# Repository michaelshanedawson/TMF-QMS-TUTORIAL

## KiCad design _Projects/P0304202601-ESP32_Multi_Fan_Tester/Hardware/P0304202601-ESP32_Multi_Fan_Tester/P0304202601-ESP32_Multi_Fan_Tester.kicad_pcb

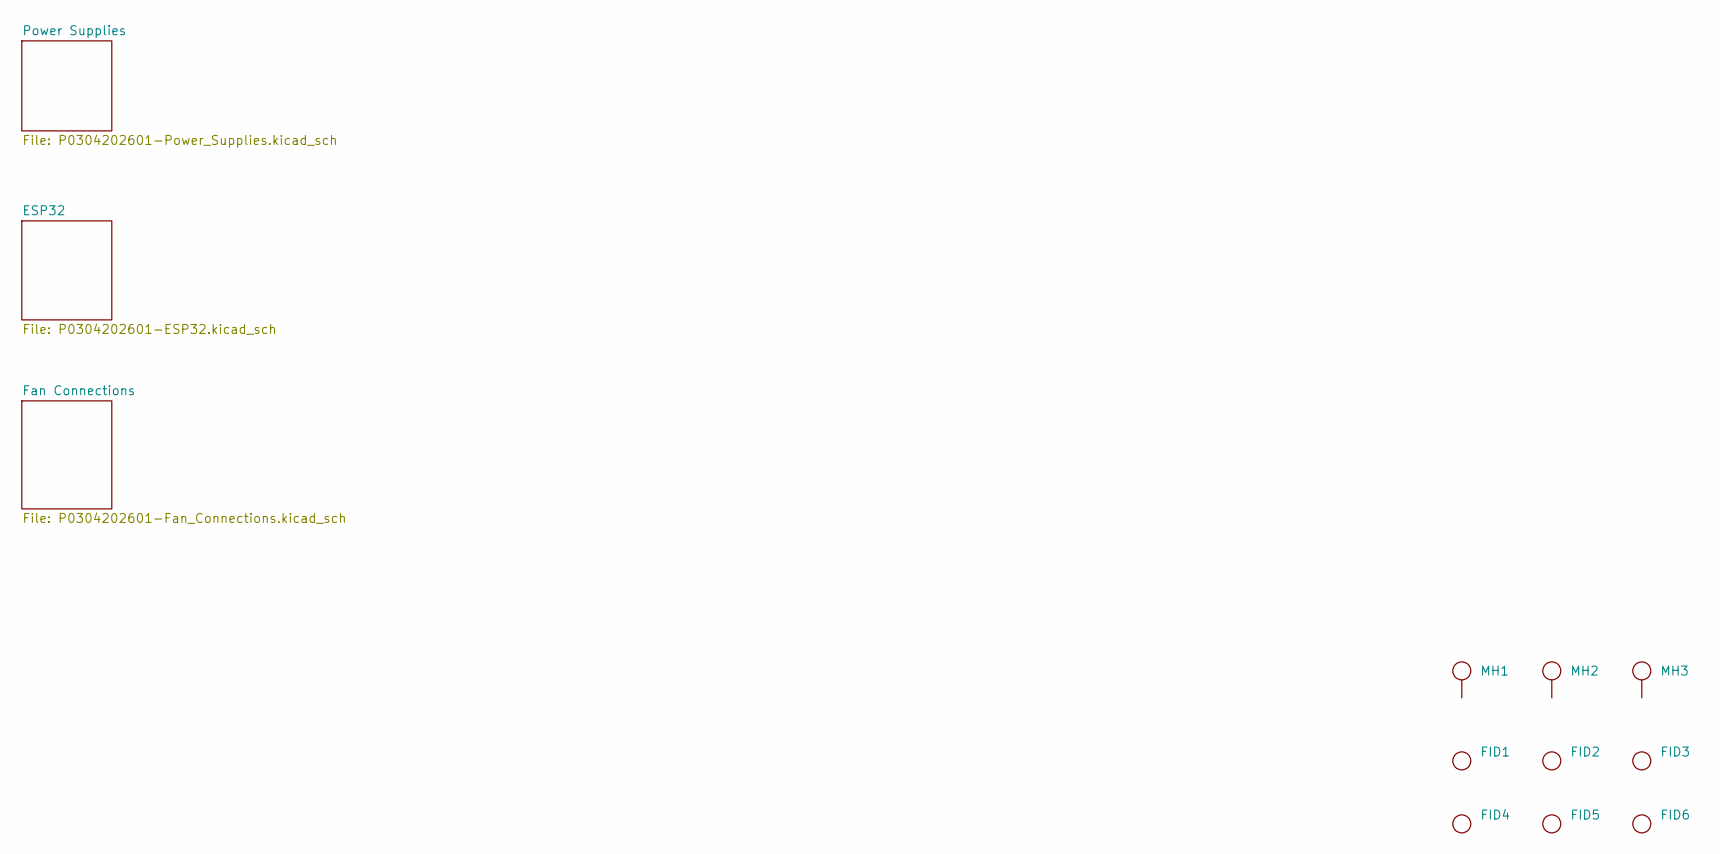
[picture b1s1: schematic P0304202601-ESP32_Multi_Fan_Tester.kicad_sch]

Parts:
FID1, FID2, FID3, FID4, FID5, FID6: FID1.0x1.5mm Round
MH1, MH2, MH3: M3MountingHole

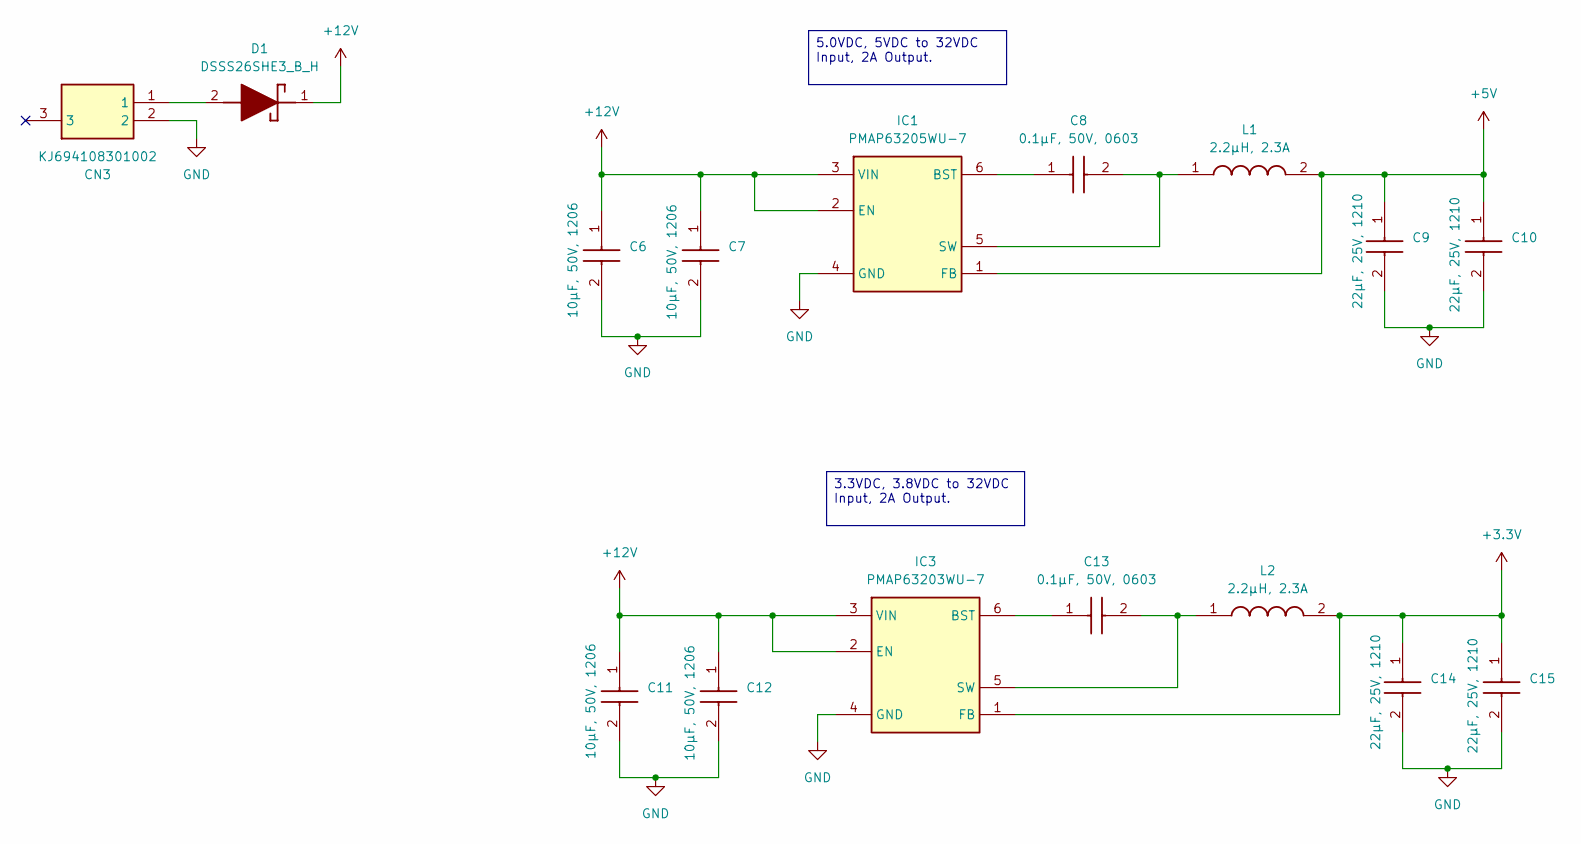
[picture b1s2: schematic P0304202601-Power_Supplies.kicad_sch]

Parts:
C6, C7, C11, C12: CC1206106050AAAX7R; CAP-1206
C8, C13: CC0603104050AAAX7R; CAP-0603
C9, C10, C14, C15: CC1210226025AAAX7R; CAP-1210
CN3: KJ694108301002
D1: DSSS26SHE3_B_H; SMA
IC1: PMAP63205WU-7; TSOT-26-6
IC3: PMAP63203WU-7; TSOT-26-6
L1, L2: LSRP2512-2R2M; IND-1005

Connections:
+3.3V: C14.1, C15.1, IC3.1 (FB), L2.2; also elsewhere on the board
+5V: C9.1, C10.1, IC1.1 (FB), L1.2; also elsewhere on the board
+12V: C6.1, C7.1, C11.1, C12.1, D1.1 (K), IC1.2 (EN), IC1.3 (VIN), IC3.2 (EN), IC3.3 (VIN); also elsewhere on the board
GND: C6.2, C7.2, C9.2, C10.2, C11.2, C12.2, C14.2, C15.2, CN3.2, IC1.4 (GND), IC3.4 (GND); also elsewhere on the board
unnamed: CN3.1, D1.2 (A)
unnamed: C8.1, IC1.6 (BST)
unnamed: C8.2, IC1.5 (SW), L1.1
unnamed: C13.1, IC3.6 (BST)
unnamed: C13.2, IC3.5 (SW), L2.1

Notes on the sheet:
5.0VDC, 5VDC to 32VDC Input, 2A Output.
3.3VDC, 3.8VDC to 32VDC Input, 2A Output.

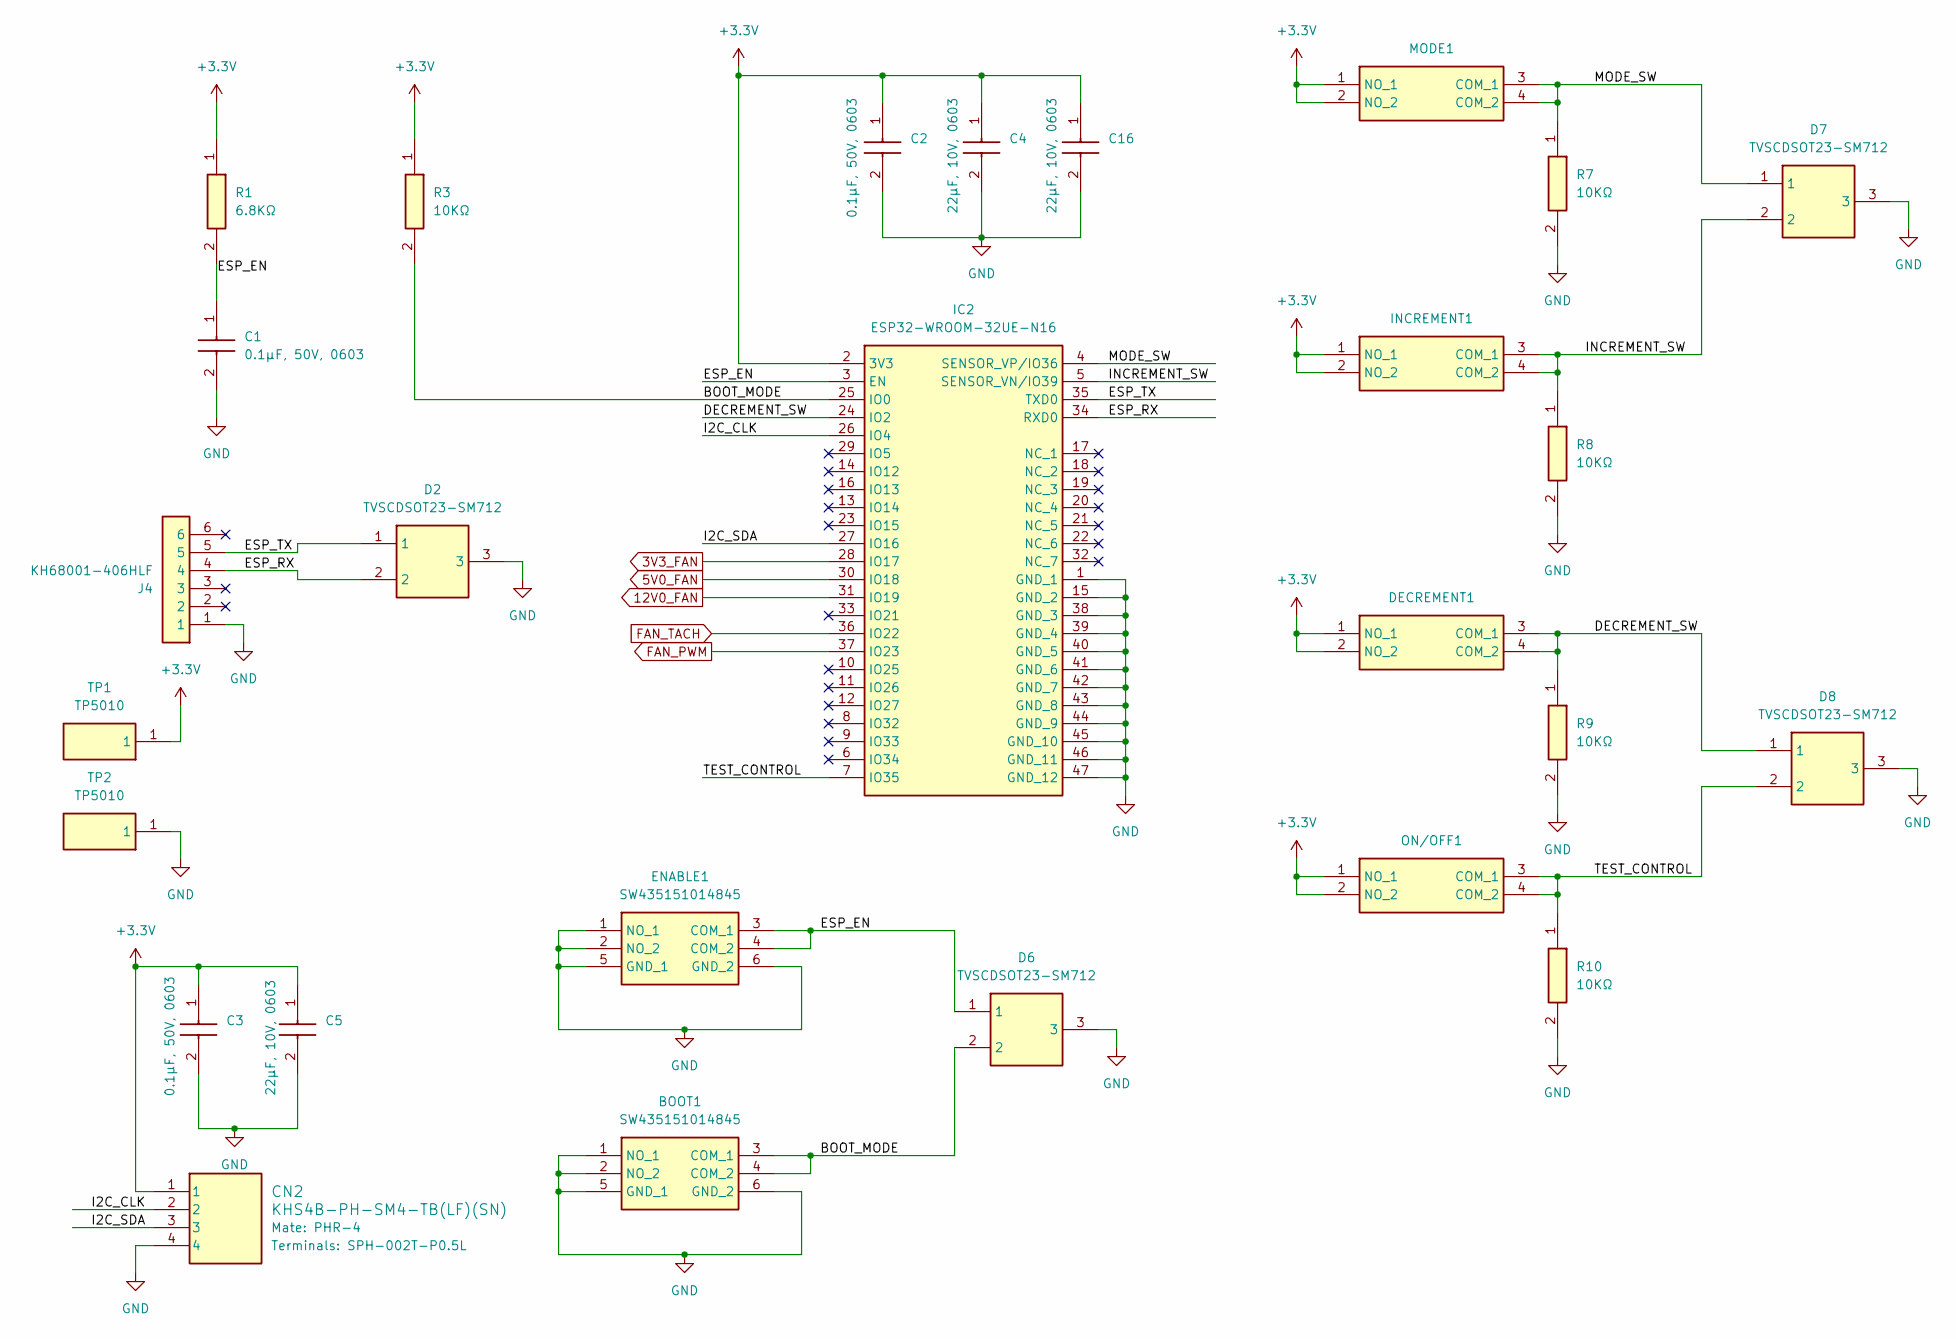
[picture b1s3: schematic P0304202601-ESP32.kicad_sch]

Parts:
BOOT1: SW435151014845; 435151014845
C1, C2, C3: CC0603104050AAAX7R; CAP-0603
C4, C5, C16: CC0603226010AABX5R; CAP-0603
CN2: KHS4B-PH-SM4-TB(LF)(SN); S4B-PH-SM4-TB
D2, D6, D7, D8: TVSCDSOT23-SM712; SOT-23-3
DECREMENT1: TS14121260BK260SCRD
ENABLE1: SW435151014845; 435151014845
IC2: ESP32-WROOM-32UE-N16; ESP32WROOM32UE
INCREMENT1: TS14121260BK260SCRD
J4: KH68001-406HLF; 6x1HDR2.54mm
MODE1: TS14121260BK260SCRD
ON/OFF1: TS14121260BK260SCRD
R1: RC0603682075AAA; RES-0603
R3, R7, R8, R9, R10: RC060310K2075AAA; RES-0603
TP1, TP2: TP5010; 5010

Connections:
3V3_FAN: IC2.28 (IO17); also elsewhere on the board
5V0_FAN: IC2.30 (IO18); also elsewhere on the board
12V0_FAN: IC2.31 (IO19); also elsewhere on the board
+3.3V: C2.1, C3.1, C4.1, C5.1, C16.1, CN2.1, DECREMENT1.1 (NO_1), DECREMENT1.2 (NO_2), IC2.2 (3V3), INCREMENT1.1 (NO_1), INCREMENT1.2 (NO_2), MODE1.1 (NO_1), MODE1.2 (NO_2), ON/OFF1.1 (NO_1), ON/OFF1.2 (NO_2), R1.1, R3.1, TP1.1 (1_1); also elsewhere on the board
/ESP32/BOOT_MODE: BOOT1.3 (COM_1), BOOT1.4 (COM_2), D6.2, IC2.25 (IO0), R3.2
/ESP32/DECREMENT_SW: D8.1, DECREMENT1.3 (COM_1), DECREMENT1.4 (COM_2), IC2.24 (IO2), R9.1
/ESP32/ESP_EN: C1.1, D6.1, ENABLE1.3 (COM_1), ENABLE1.4 (COM_2), IC2.3 (EN), R1.2
/ESP32/ESP_RX: D2.2, IC2.34 (RXD0), J4.4
/ESP32/ESP_TX: D2.1, IC2.35 (TXD0), J4.5
/ESP32/I2C_CLK: CN2.2, IC2.26 (IO4)
/ESP32/I2C_SDA: CN2.3, IC2.27 (IO16)
/ESP32/INCREMENT_SW: D7.2, IC2.5 (SENSOR_VN/IO39), INCREMENT1.3 (COM_1), INCREMENT1.4 (COM_2), R8.1
/ESP32/MODE_SW: D7.1, IC2.4 (SENSOR_VP/IO36), MODE1.3 (COM_1), MODE1.4 (COM_2), R7.1
/ESP32/TEST_CONTROL: D8.2, IC2.7 (IO35), ON/OFF1.3 (COM_1), ON/OFF1.4 (COM_2), R10.1
FAN_PWM: IC2.37 (IO23); also elsewhere on the board
FAN_TACH: IC2.36 (IO22); also elsewhere on the board
GND: BOOT1.1 (NO_1), BOOT1.2 (NO_2), BOOT1.5 (GND_1), BOOT1.6 (GND_2), C1.2, C2.2, C3.2, C4.2, C5.2, C16.2, CN2.4, D2.3, D6.3, D7.3, D8.3, ENABLE1.1 (NO_1), ENABLE1.2 (NO_2), ENABLE1.5 (GND_1), ENABLE1.6 (GND_2), IC2.1 (GND_1), IC2.15 (GND_2), IC2.38 (GND_3), IC2.39 (GND_4), IC2.40 (GND_5), IC2.41 (GND_6), IC2.42 (GND_7), IC2.43 (GND_8), IC2.44 (GND_9), IC2.45 (GND_10), IC2.46 (GND_11), IC2.47 (GND_12), J4.1, R7.2, R8.2, R9.2, R10.2, TP2.1 (1_1); also elsewhere on the board

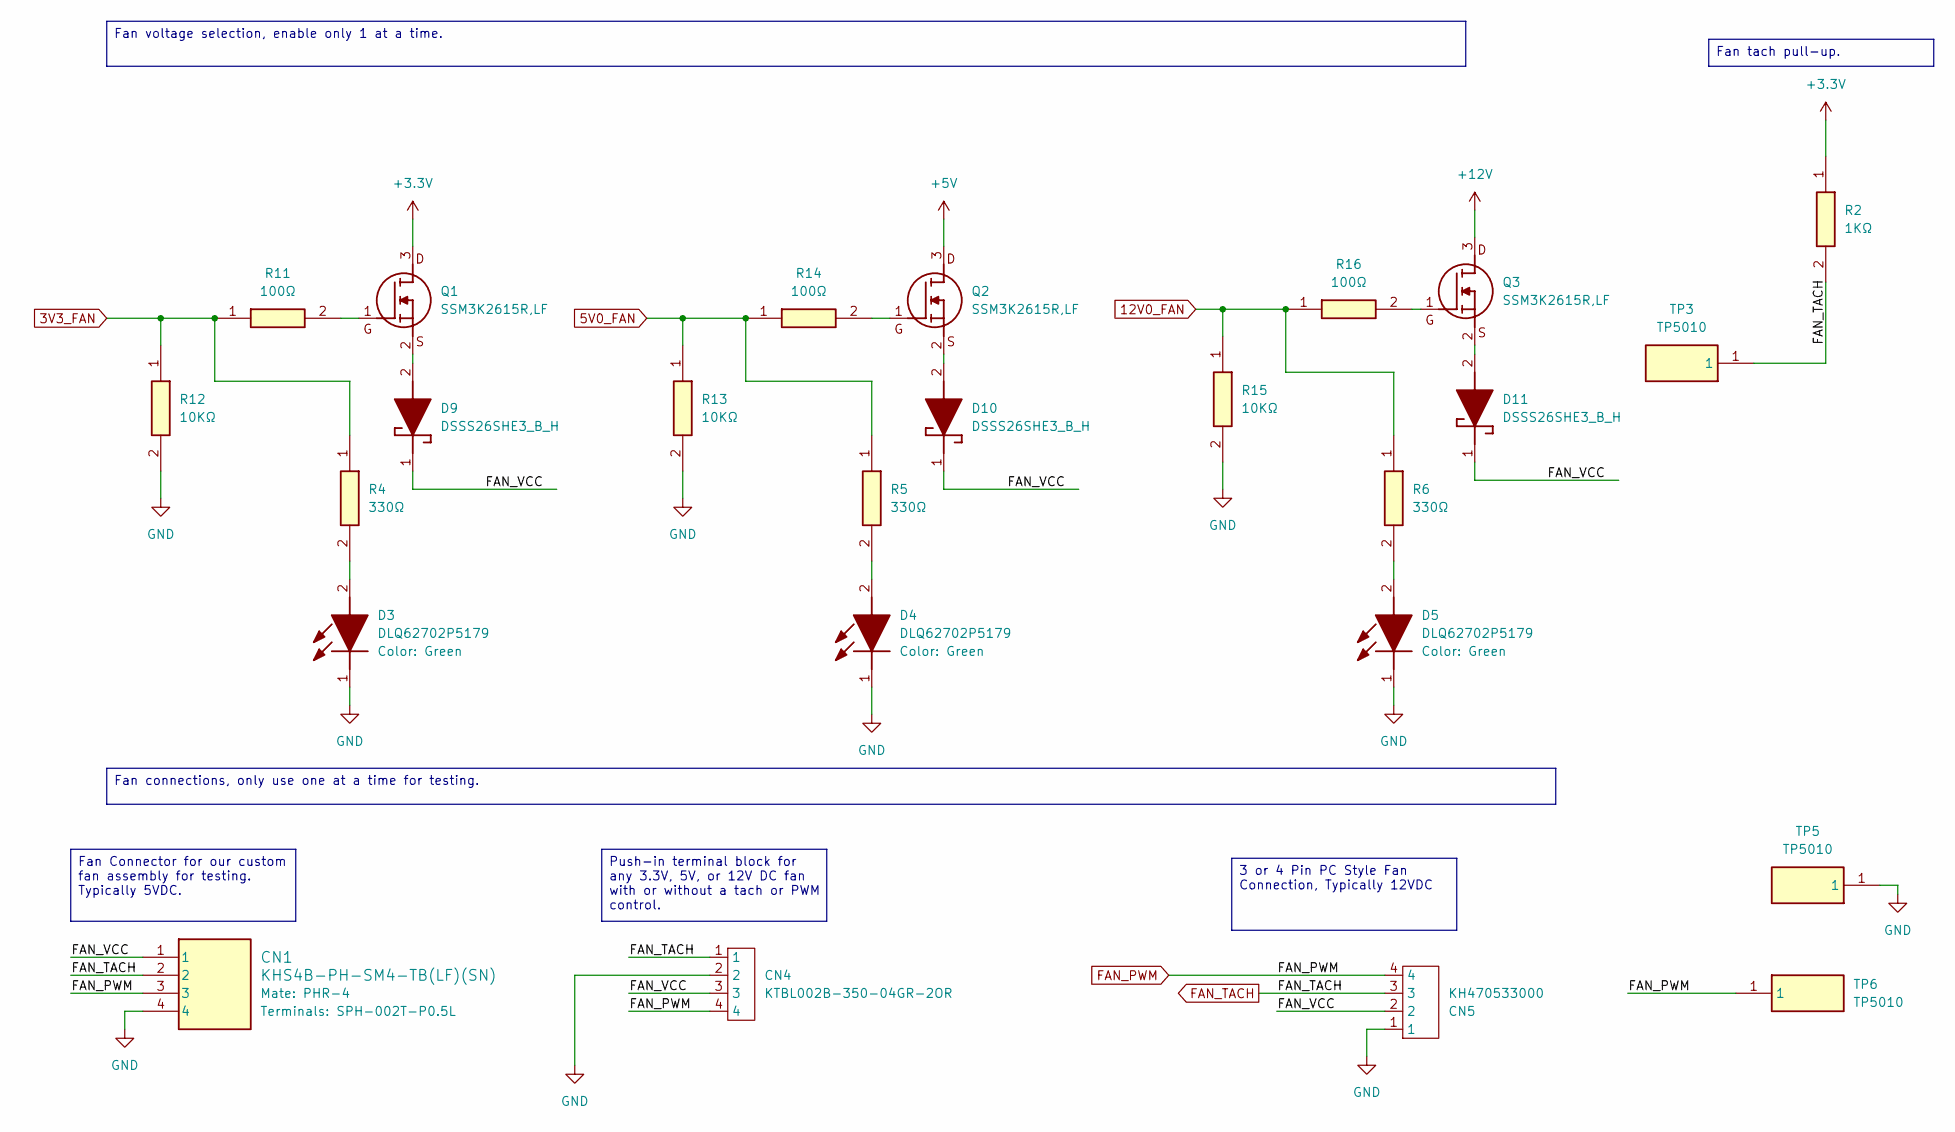
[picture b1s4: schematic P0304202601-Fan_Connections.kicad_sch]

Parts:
CN1: KHS4B-PH-SM4-TB(LF)(SN); S4B-PH-SM4-TB
CN4: KTBL002B-350-04GR-2OR; KTBTBL002B35004GR2OR
CN5: KH470533000
D3, D4, D5: DLQ62702P5179; LED-0805
D9, D10, D11: DSSS26SHE3_B_H; SMA
Q1, Q2, Q3: SSM3K2615R,LF; SOT-23F-3
R2: RC06031K0075AAA; RES-0603
R4, R5, R6: RC0603330075AAA; RES-0603
R11, R14, R16: 100Ω; RES-0603
R12, R13, R15: RC060310K2075AAA; RES-0603
TP3, TP5, TP6: TP5010; 5010

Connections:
3V3_FAN: R4.1, R11.1, R12.1; also elsewhere on the board
5V0_FAN: R5.1, R13.1, R14.1; also elsewhere on the board
12V0_FAN: R6.1, R15.1, R16.1; also elsewhere on the board
+3.3V: Q1.3 (D), R2.1; also elsewhere on the board
+5V: Q2.3 (D); also elsewhere on the board
+12V: Q3.3 (D); also elsewhere on the board
/Fan Connections/FAN_VCC: CN1.1, CN4.3, CN5.2, D9.1 (K), D10.1 (K), D11.1 (K)
FAN_PWM: CN1.3, CN4.4, CN5.4, TP6.1 (1_1); also elsewhere on the board
FAN_TACH: CN1.2, CN4.1, CN5.3, R2.2, TP3.1 (1_1); also elsewhere on the board
GND: CN1.4, CN4.2, CN5.1, D3.1 (K), D4.1 (K), D5.1 (K), R12.2, R13.2, R15.2, TP5.1 (1_1); also elsewhere on the board
unnamed: D3.2 (A), R4.2
unnamed: D4.2 (A), R5.2
unnamed: D5.2 (A), R6.2
unnamed: D9.2 (A), Q1.2 (S)
unnamed: D10.2 (A), Q2.2 (S)
unnamed: D11.2 (A), Q3.2 (S)
unnamed: Q1.1 (G), R11.2
unnamed: Q2.1 (G), R14.2
unnamed: Q3.1 (G), R16.2

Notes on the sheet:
Fan Connector for our custom fan assembly for testing. Typically 5VDC.
3 or 4 Pin PC Style Fan Connection, Typically 12VDC
Fan tach pull-up.
Fan connections, only use one at a time for testing.
Push-in terminal block for any 3.3V, 5V, or 12V DC fan with or without a tach or PWM control.
Fan voltage selection, enable only 1 at a time.

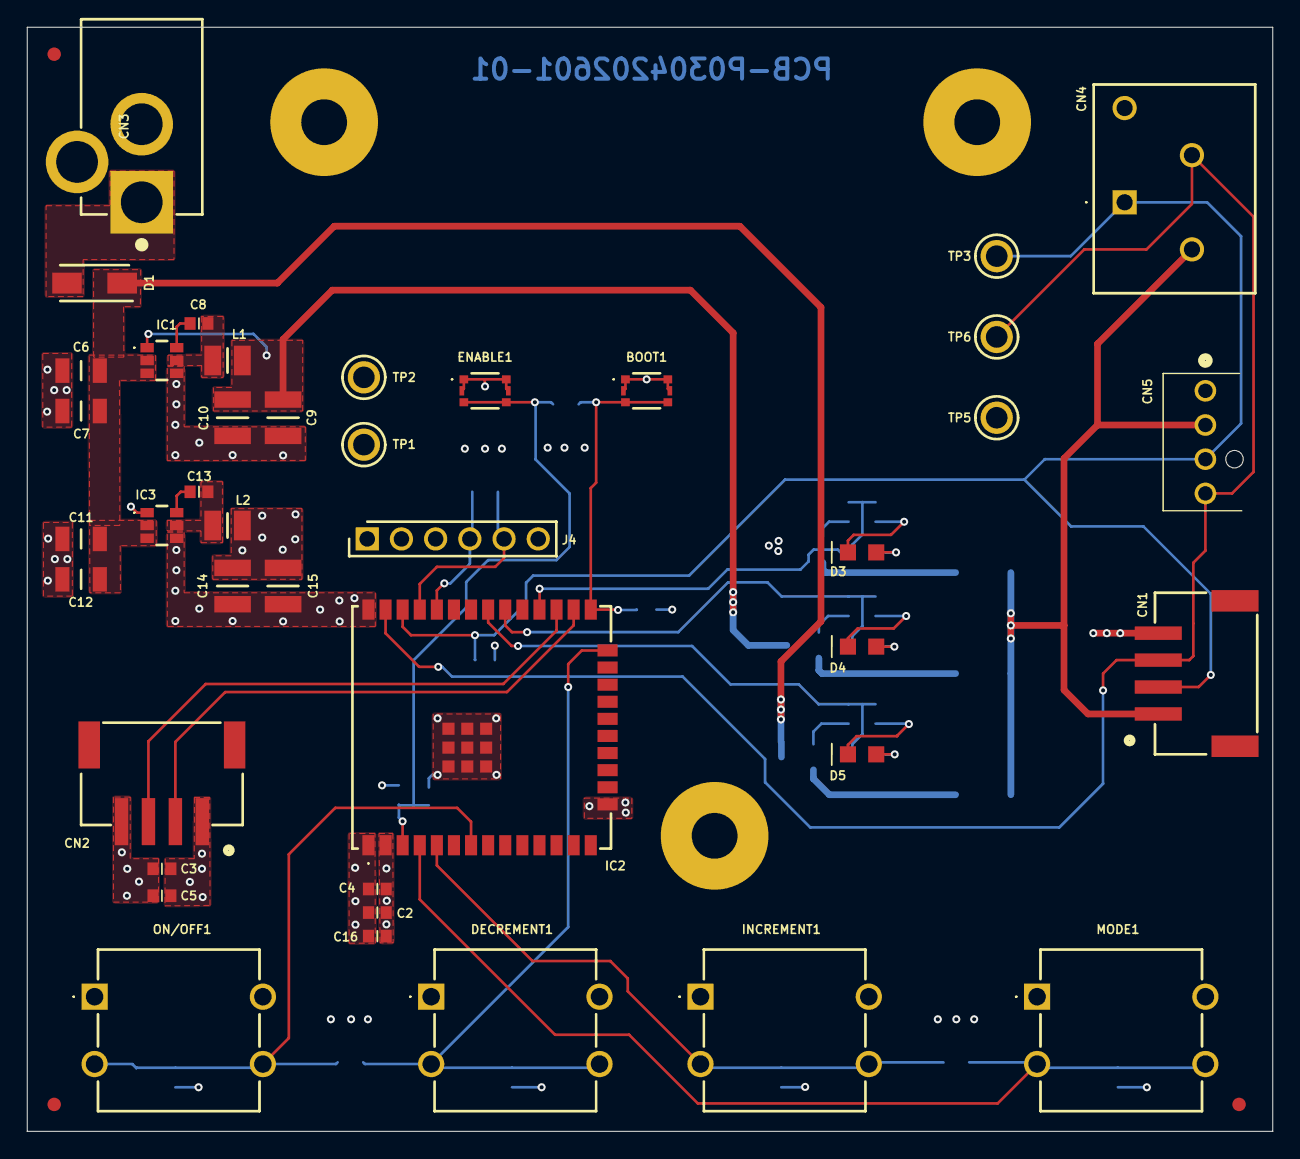
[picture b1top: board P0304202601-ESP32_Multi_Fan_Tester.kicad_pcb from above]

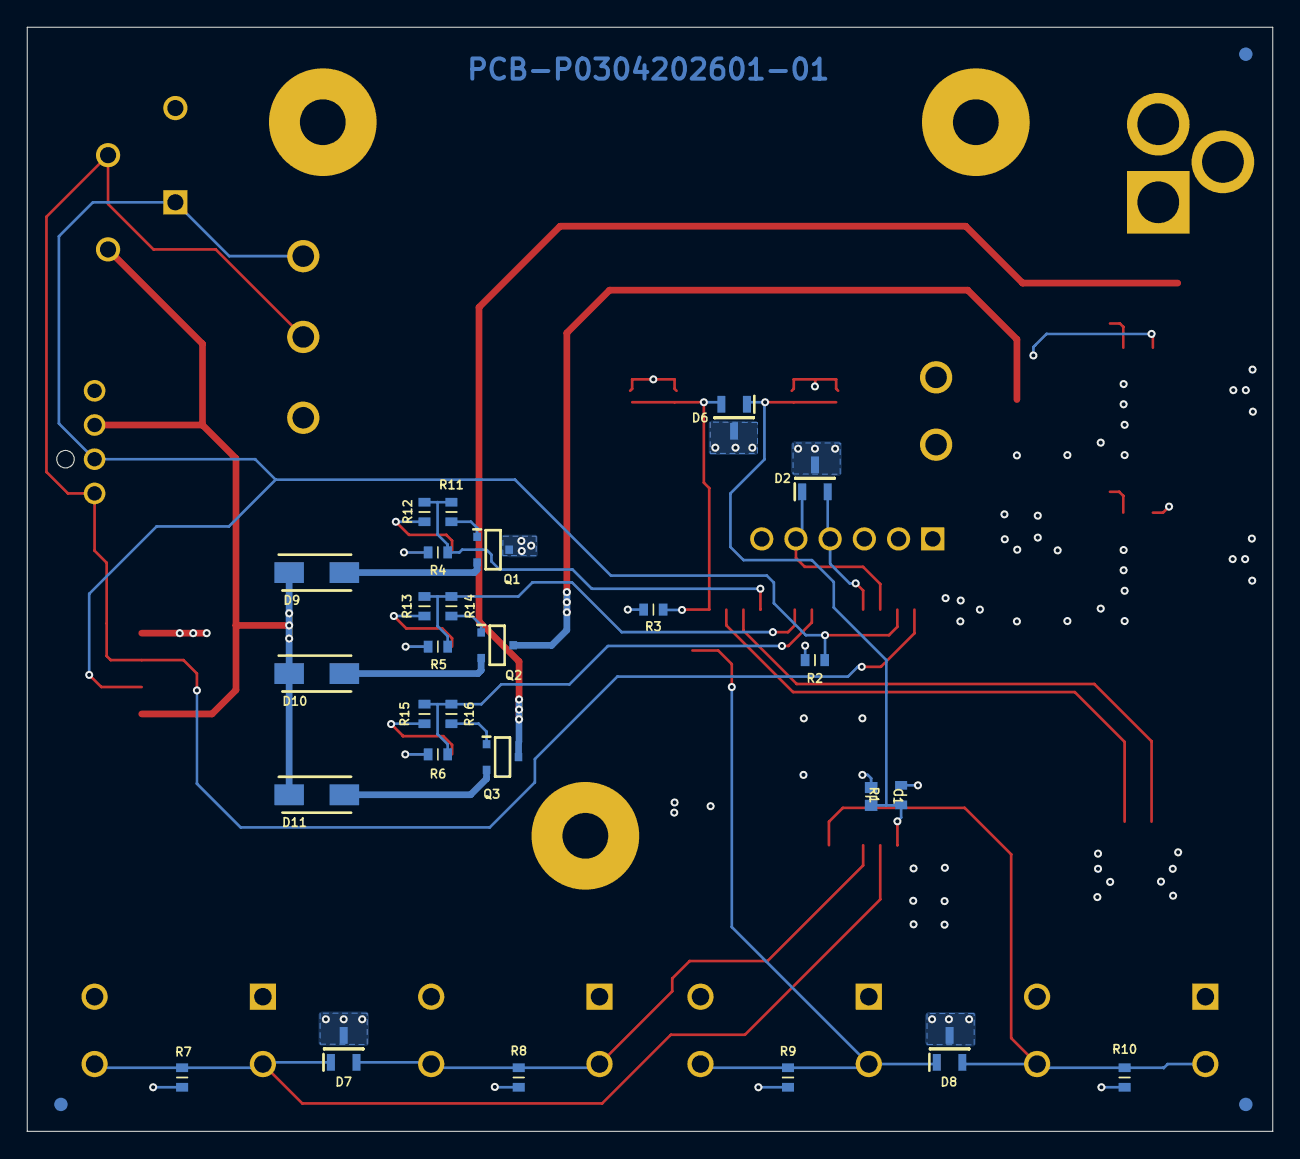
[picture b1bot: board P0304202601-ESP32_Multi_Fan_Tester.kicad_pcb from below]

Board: 4 copper layers, 92.5 x 82.0 mm, 77 parts (30 on the bottom side), 34 nets.

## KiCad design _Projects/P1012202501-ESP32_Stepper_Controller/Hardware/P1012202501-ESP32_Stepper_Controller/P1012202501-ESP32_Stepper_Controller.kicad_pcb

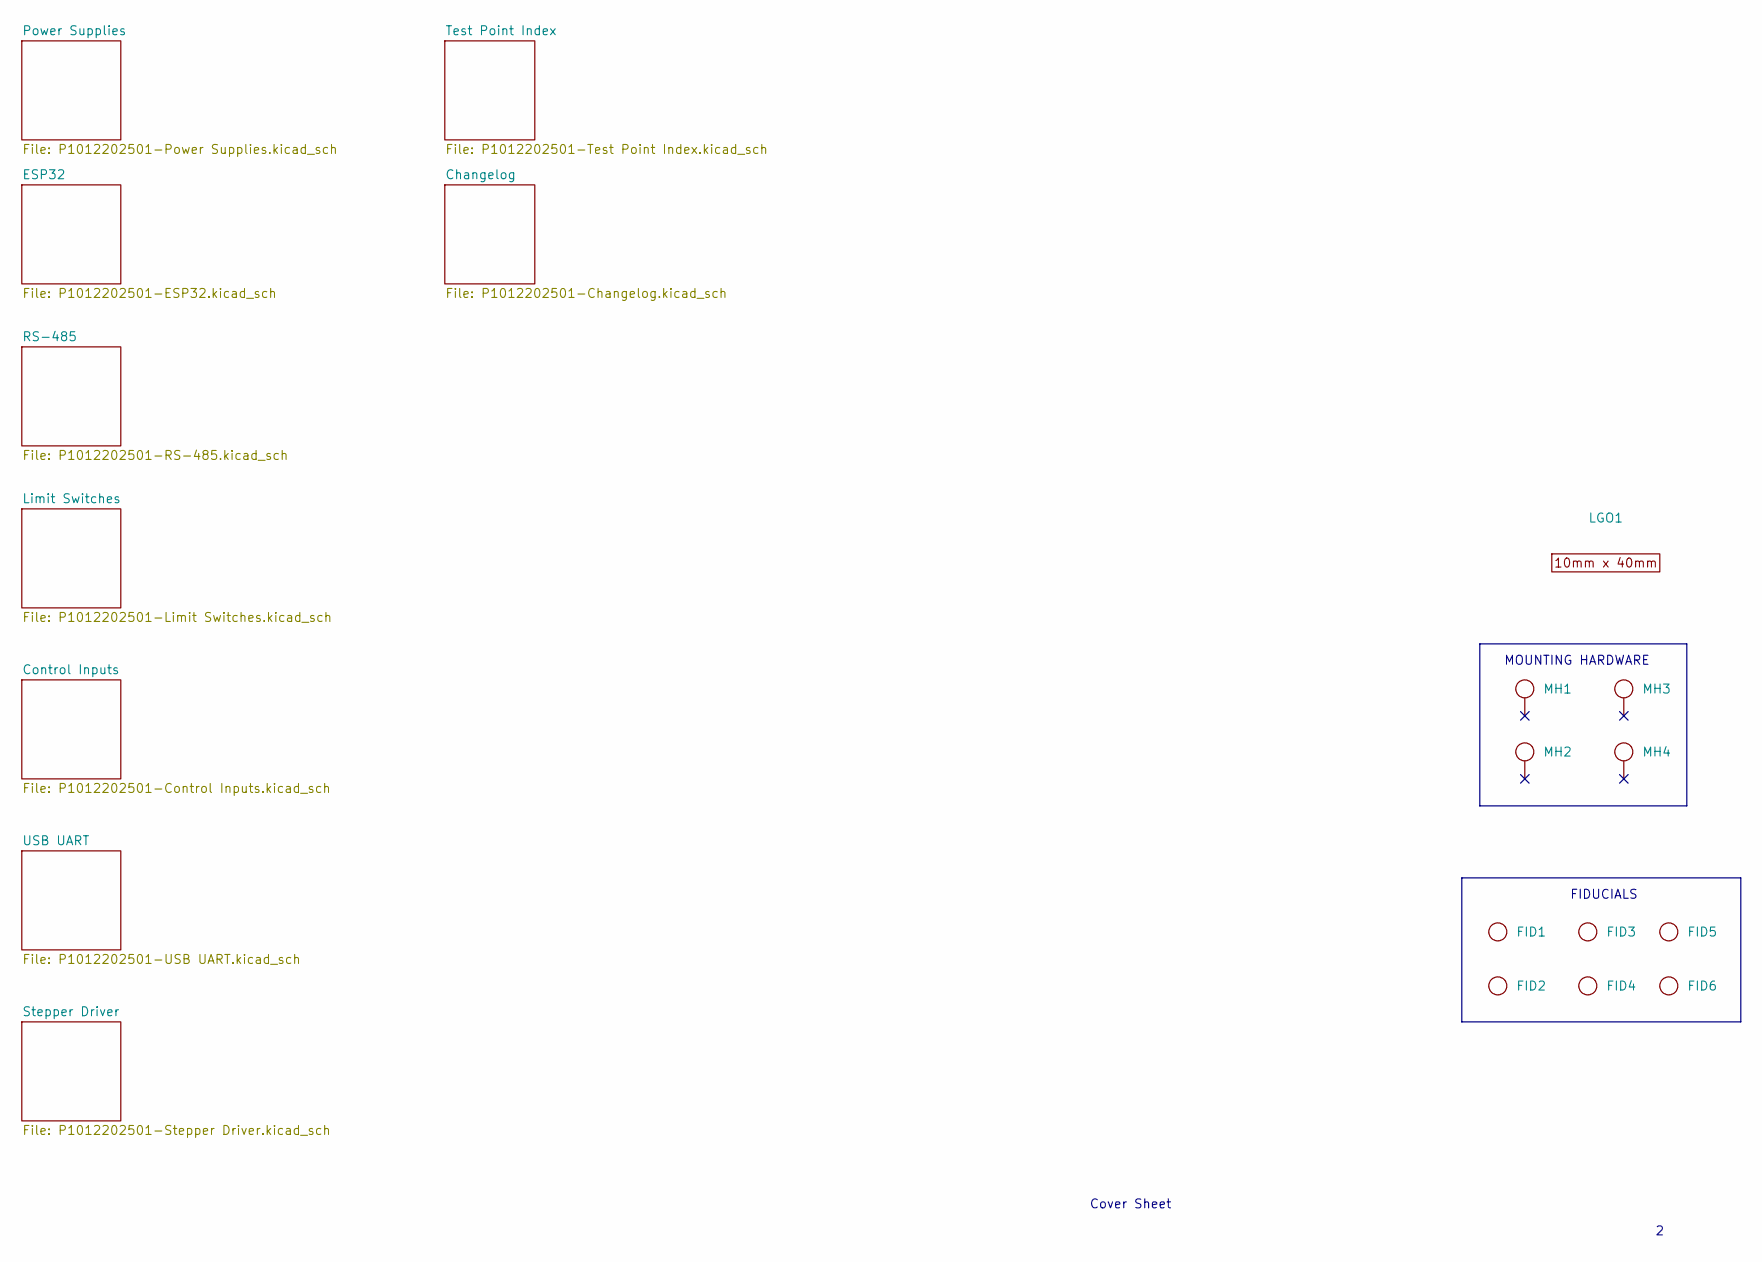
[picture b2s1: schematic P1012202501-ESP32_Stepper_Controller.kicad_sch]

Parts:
FID1, FID2, FID3, FID4, FID5, FID6: FID1.0x1.5mm Round
LGO1: Logo10x40mm
MH1, MH2, MH3, MH4: M3MountingHole

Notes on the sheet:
Cover Sheet
MOUNTING HARDWARE
FIDUCIALS

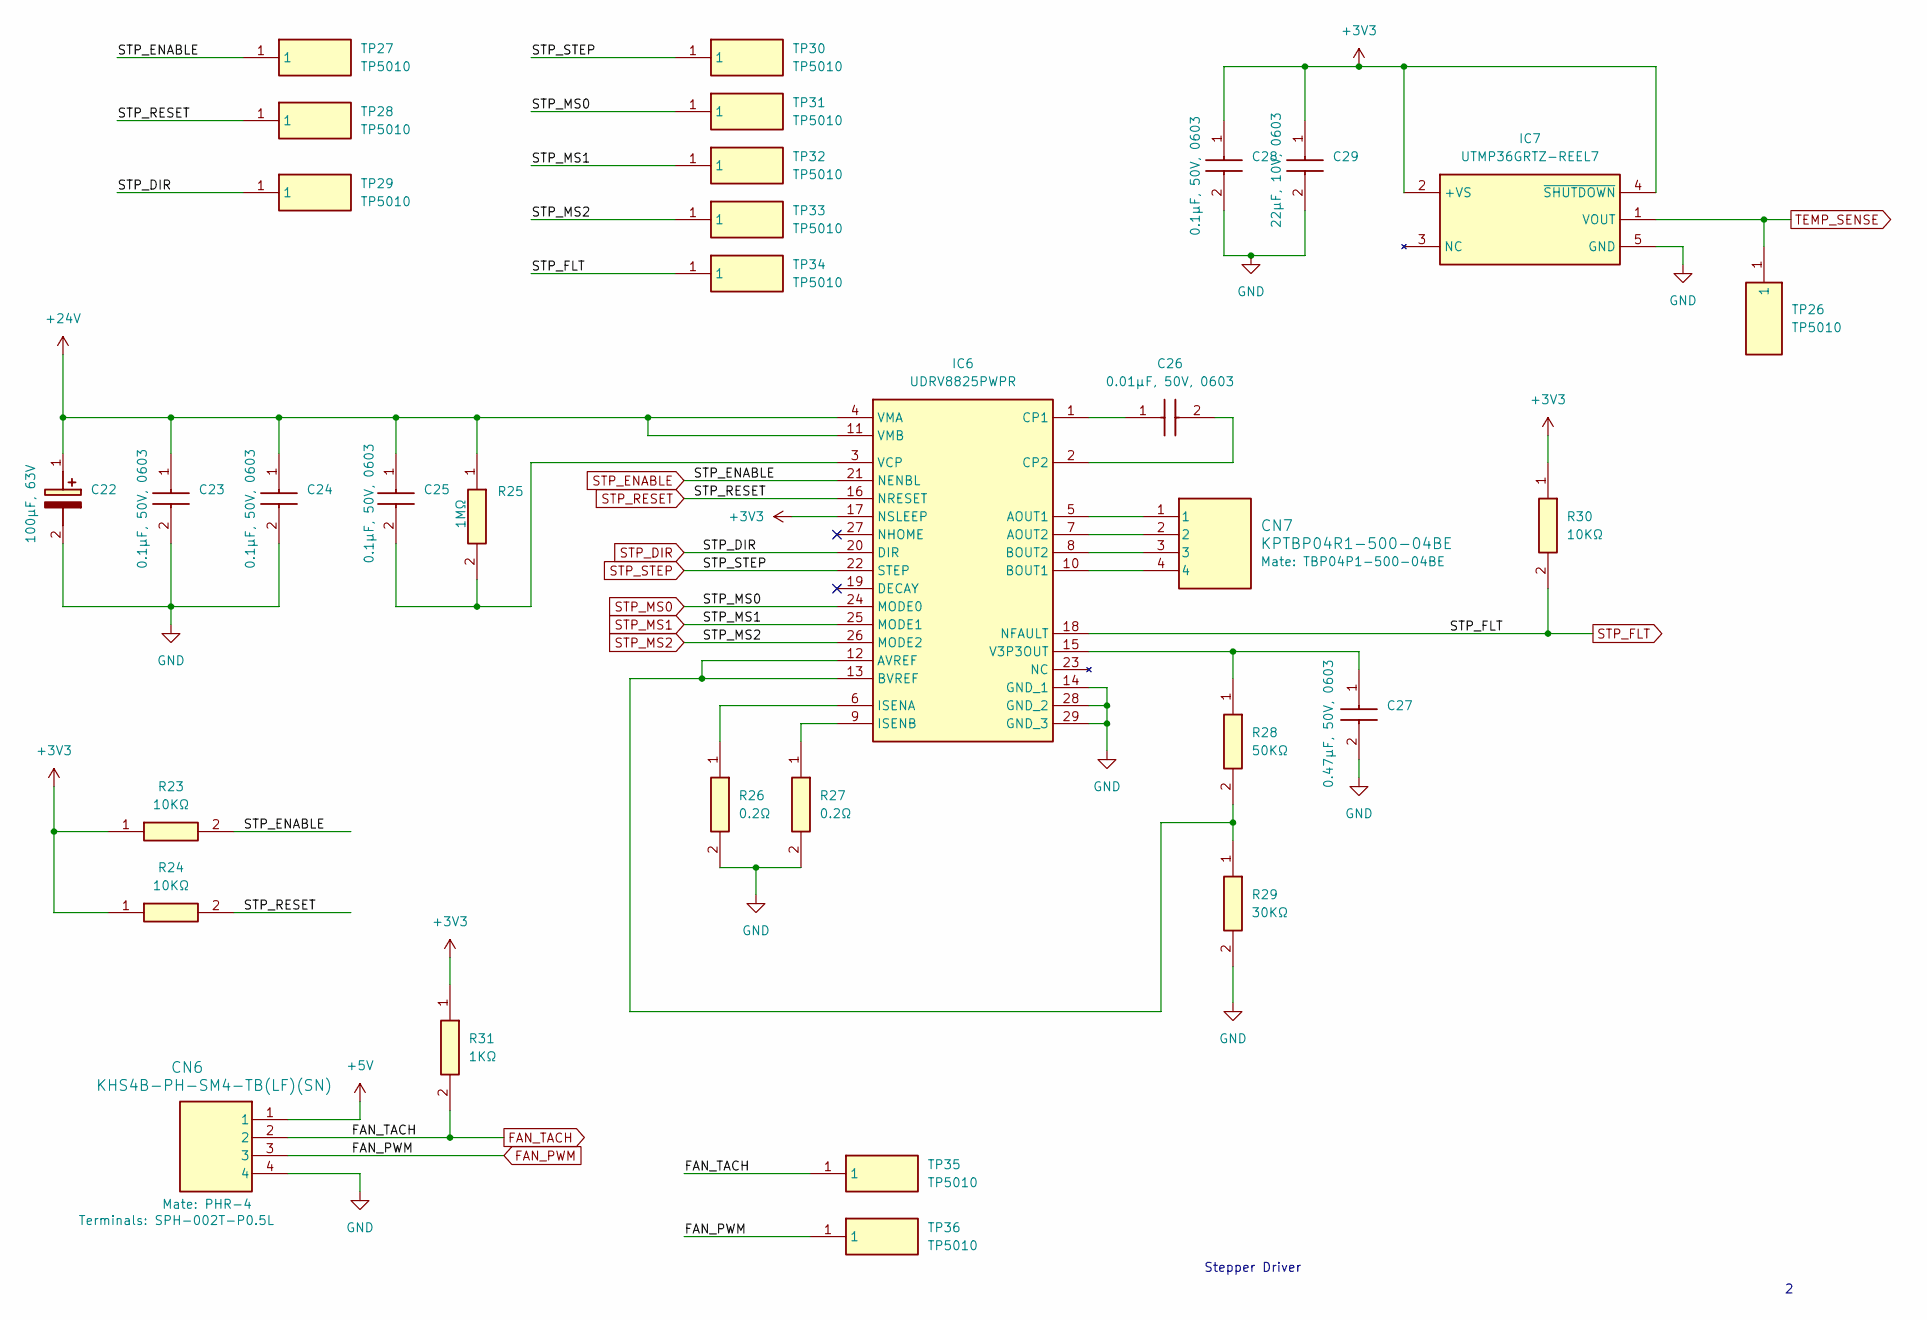
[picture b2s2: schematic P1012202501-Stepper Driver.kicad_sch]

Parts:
C22: CEA771MS107M1JLAS018; A768MS157M1HLAE024
C23, C24, C25, C28: CC0603104050AAAX7R; CAP-0603
C26: CC0603103050AAAX7R; CAP-0603
C27: CC0603474050AAAX7R; CAP-0603
C29: CC0603226010AABX5R; CAP-0603
CN6: KHS4B-PH-SM4-TB(LF)(SN); S4B-PH-SM4-TB
CN7: KPTBP04R1-500-04BE; TBP04R1-500-04BE
IC6: UDRV8825PWPR; HTSSOP-28
IC7: UTMP36GRTZ-REEL7; SOT-23-5
R23, R24, R30: RC060310K2075AAA; RES-0603
R25: RC06031M0075AAA; RES-0603
R26, R27: RC08050R2075AAE; RES-0805
R28: RC060350K075AAA; RES-0603
R29: RC060330K075AAA; RES-0603
R31: RC06031K0075AAA; RES-0603
TP26, TP27, TP28, TP29, TP30, TP31, TP32, TP33, TP34, TP35, TP36: TP5010; 5010

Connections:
+3V3: C28.1, C29.1, IC6.17 (NSLEEP), IC7.2 (+VS), IC7.4 (~SHUTDOWN), R23.1, R24.1, R30.1, R31.1; also elsewhere on the board
+5V: CN6.1; also elsewhere on the board
+24V: C22.1 (+), C23.1, C24.1, C25.1, IC6.4 (VMA), IC6.11 (VMB), R25.1; also elsewhere on the board
FAN_PWM: CN6.3, TP36.1; also elsewhere on the board
FAN_TACH: CN6.2, R31.2, TP35.1; also elsewhere on the board
GND: C22.2 (-), C23.2, C24.2, C27.2, C28.2, C29.2, CN6.4, IC6.14 (GND_1), IC6.28 (GND_2), IC6.29 (GND_3), IC7.5 (GND), R26.2, R27.2, R29.2; also elsewhere on the board
unnamed: CN7.1, IC6.5 (AOUT1)
unnamed: CN7.2, IC6.7 (AOUT2)
unnamed: IC6.12 (AVREF), IC6.13 (BVREF), R28.2, R29.1
unnamed: CN7.4, IC6.10 (BOUT1)
unnamed: CN7.3, IC6.8 (BOUT2)
unnamed: C26.1, IC6.1 (CP1)
unnamed: C26.2, IC6.2 (CP2)
unnamed: IC6.6 (ISENA), R26.1
unnamed: IC6.9 (ISENB), R27.1
unnamed: C27.1, IC6.15 (V3P3OUT), R28.1
unnamed: C25.2, IC6.3 (VCP), R25.2
STP_DIR: IC6.20 (DIR), TP29.1; also elsewhere on the board
STP_ENABLE: IC6.21 (NENBL), R23.2, TP27.1; also elsewhere on the board
STP_FLT: IC6.18 (NFAULT), R30.2, TP34.1; also elsewhere on the board
STP_MS0: IC6.24 (MODE0), TP31.1; also elsewhere on the board
STP_MS1: IC6.25 (MODE1), TP32.1; also elsewhere on the board
STP_MS2: IC6.26 (MODE2), TP33.1; also elsewhere on the board
STP_RESET: IC6.16 (NRESET), R24.2, TP28.1; also elsewhere on the board
STP_STEP: IC6.22 (STEP), TP30.1; also elsewhere on the board
TEMP_SENSE: IC7.1 (VOUT), TP26.1; also elsewhere on the board

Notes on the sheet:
Stepper Driver

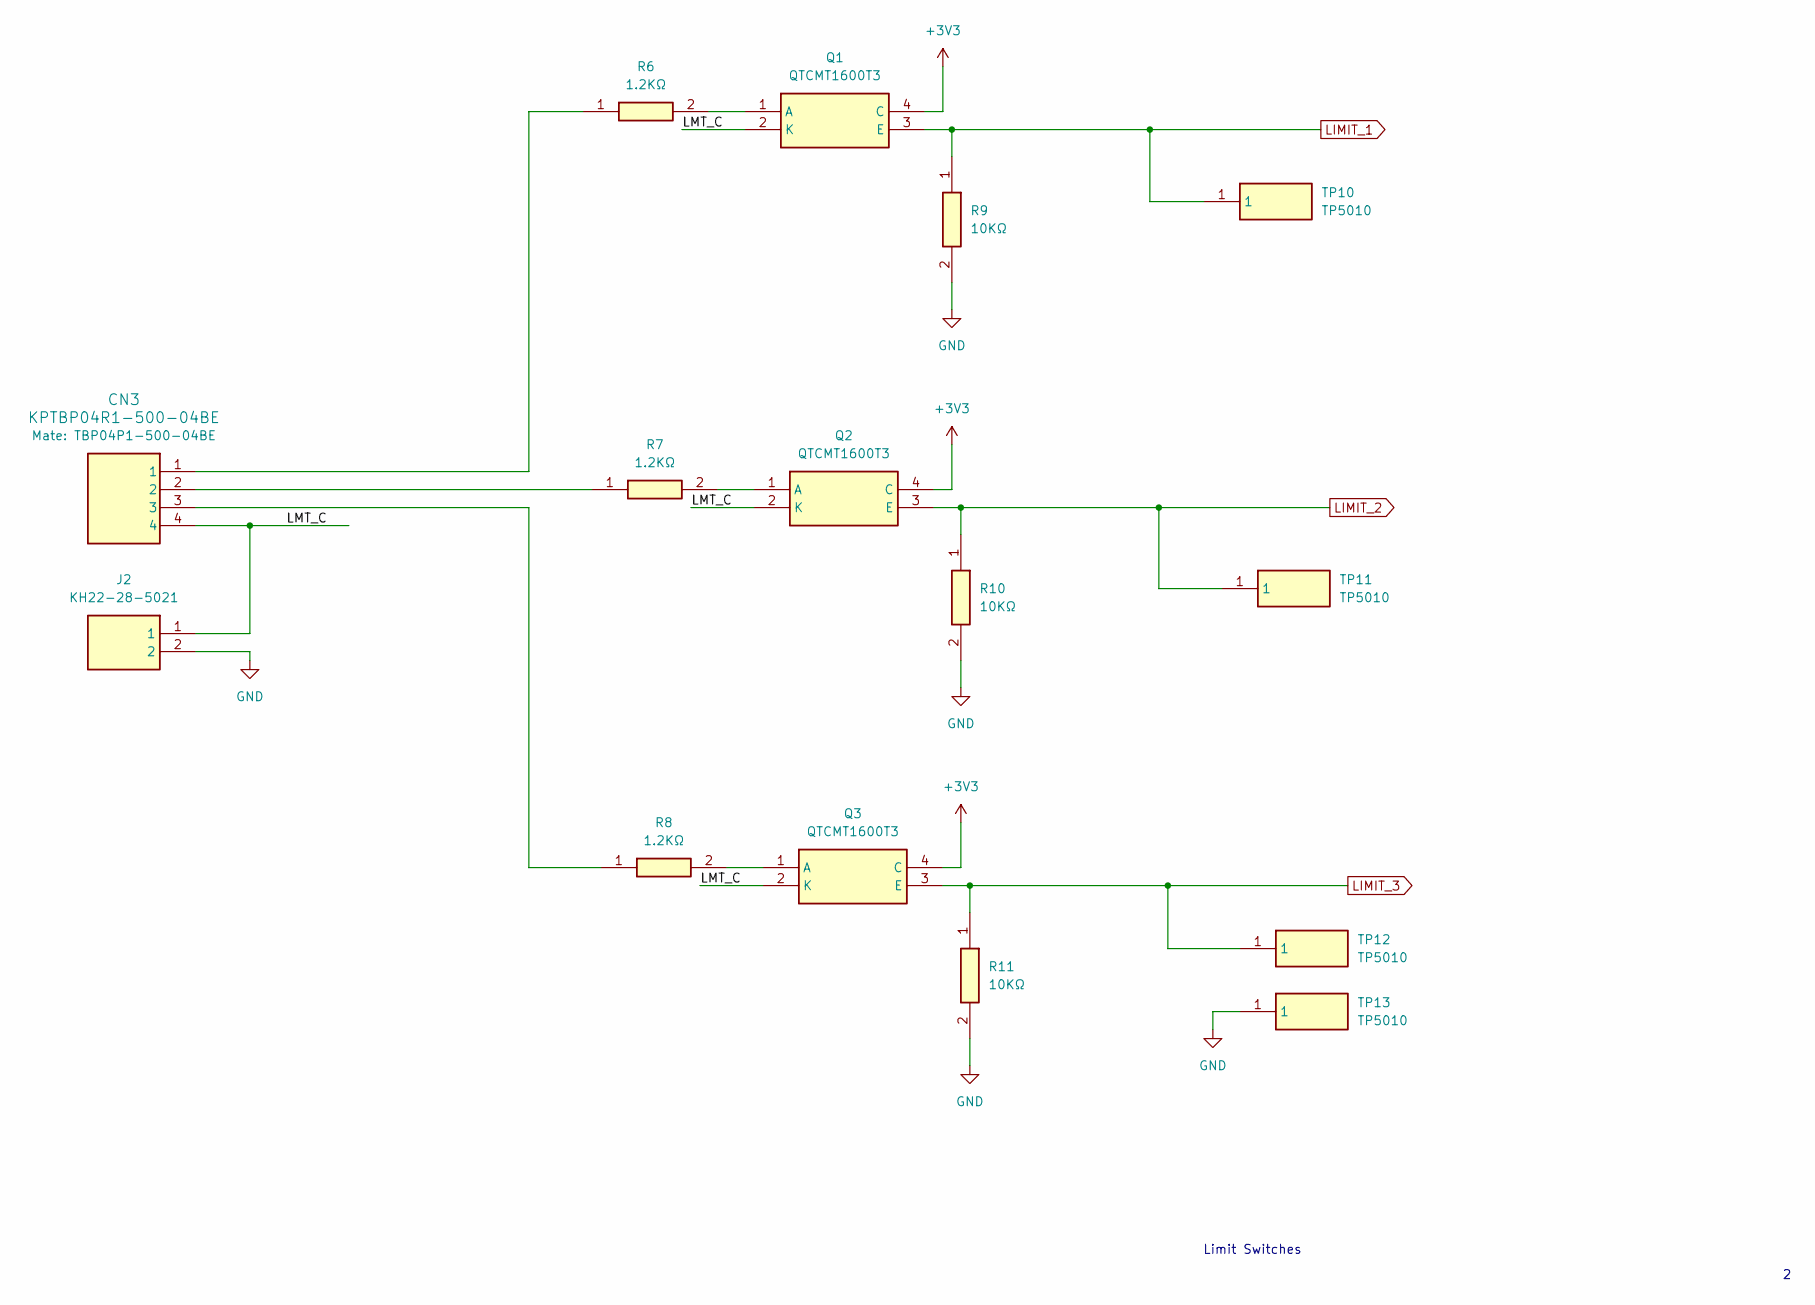
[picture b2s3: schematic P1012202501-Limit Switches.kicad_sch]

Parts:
CN3: KPTBP04R1-500-04BE; TBP04R1-500-04BE
J2: KH22-28-5021; 2x1HDR2.54mm
Q1, Q2, Q3: QTCMT1600T3; TCMT1600T3
R6, R7, R8: RC12101K2200AAC; RES-1210
R9, R10, R11: RC060310K2075AAA; RES-0603
TP10, TP11, TP12, TP13: TP5010; 5010

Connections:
+3V3: Q1.4 (C), Q2.4 (C), Q3.4 (C); also elsewhere on the board
/Limit Switches/LMT_C: CN3.4, J2.1, Q1.2 (K), Q2.2 (K), Q3.2 (K)
GND: J2.2, R9.2, R10.2, R11.2, TP13.1; also elsewhere on the board
LIMIT_1: Q1.3 (E), R9.1, TP10.1; also elsewhere on the board
LIMIT_2: Q2.3 (E), R10.1, TP11.1; also elsewhere on the board
LIMIT_3: Q3.3 (E), R11.1, TP12.1; also elsewhere on the board
unnamed: CN3.1, R6.1
unnamed: CN3.2, R7.1
unnamed: CN3.3, R8.1
unnamed: Q1.1 (A), R6.2
unnamed: Q2.1 (A), R7.2
unnamed: Q3.1 (A), R8.2

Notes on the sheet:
Limit Switches
